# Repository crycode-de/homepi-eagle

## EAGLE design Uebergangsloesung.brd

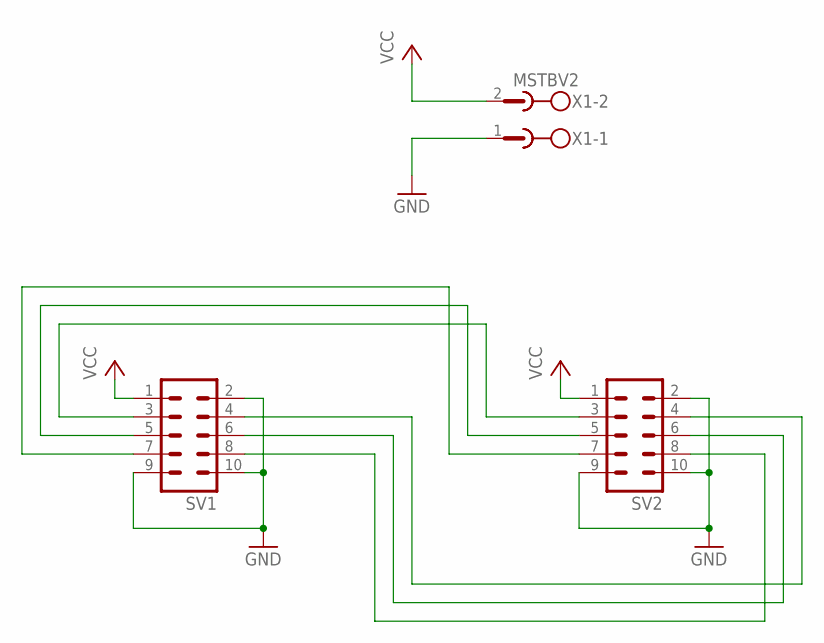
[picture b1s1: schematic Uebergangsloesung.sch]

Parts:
SV1, SV2: ML10
X1: MSTBV2

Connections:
GND: SV1.2, SV1.9, SV1.10, SV2.2, SV2.9, SV2.10, X1.1
unnamed: SV1.3, SV2.3
unnamed: SV1.5, SV2.5
unnamed: SV1.7, SV2.7
unnamed: SV1.4, SV2.4
unnamed: SV1.6, SV2.6
unnamed: SV1.8, SV2.8
VCC: SV1.1, SV2.1, X1.2

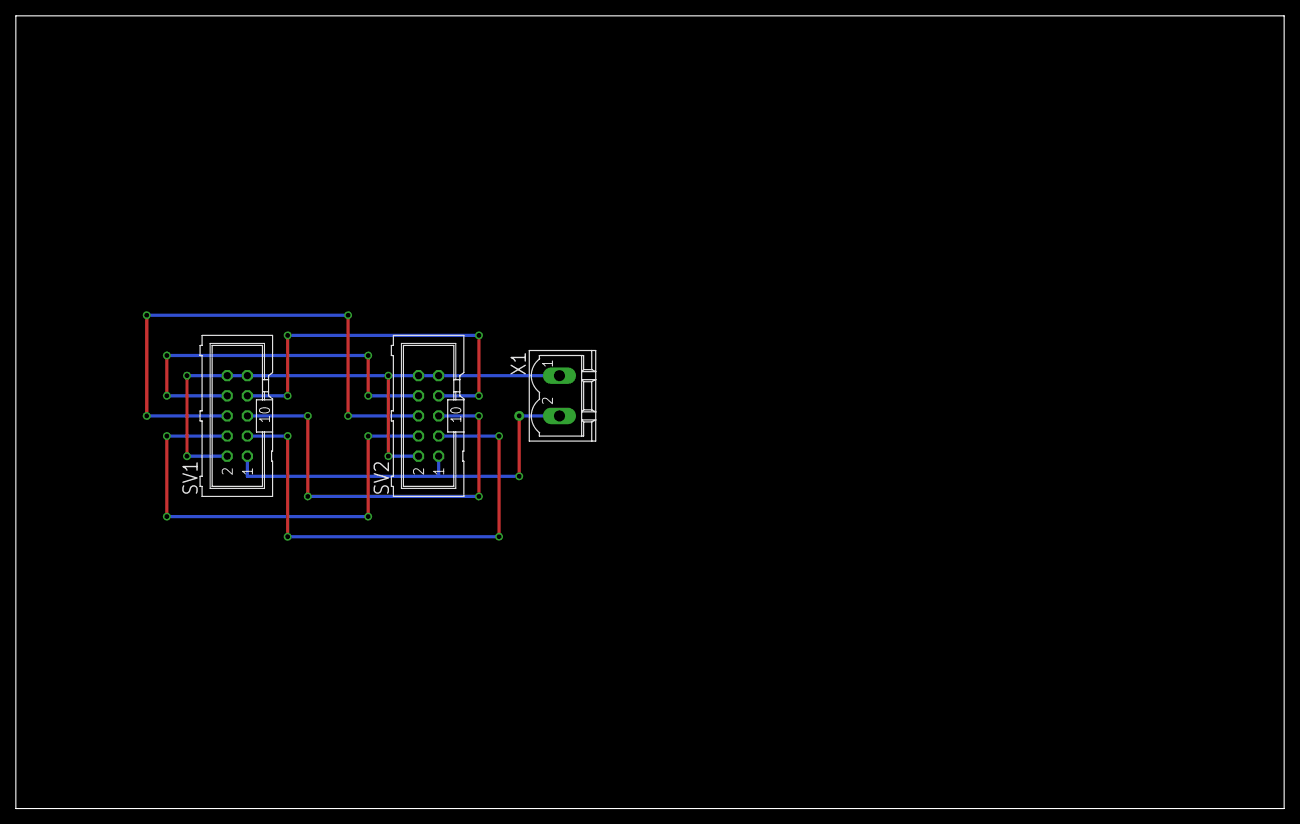
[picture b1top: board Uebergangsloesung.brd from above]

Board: 2 copper layers, 160.0 x 100.0 mm, 3 parts (0 on the bottom side), 8 nets.
